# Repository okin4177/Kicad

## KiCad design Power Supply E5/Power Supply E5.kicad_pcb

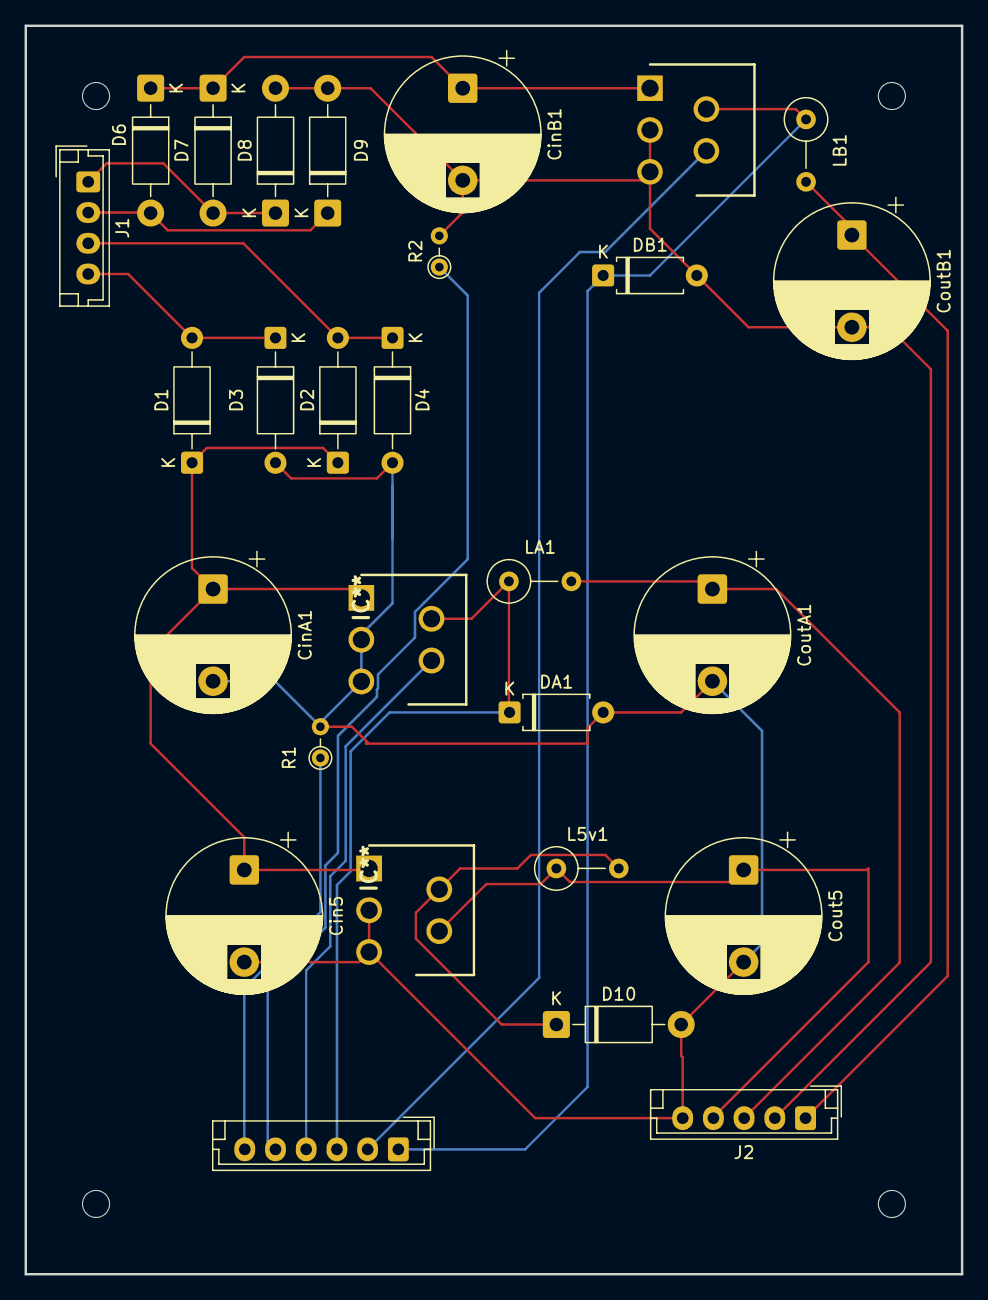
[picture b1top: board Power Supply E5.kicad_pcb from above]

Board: 2 copper layers, 76.2 x 101.6 mm, 30 parts (0 on the bottom side), 18 nets.

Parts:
Cin5: 100uF; CP_Radial_D12.5mm_P7.50mm
CinA1: 680uF; CP_Radial_D12.5mm_P7.50mm
CinB1: 100uF; CP_Radial_D12.5mm_P7.50mm
Cout5: 330uF; CP_Radial_D12.5mm_P7.50mm
CoutA1: 330uF; CP_Radial_D12.5mm_P7.50mm
CoutB1: 330uF; CP_Radial_D12.5mm_P7.50mm
D1, D2, D3, D4: 1N5059; D_A-405_P10.16mm_Horizontal
D6, D7, D8, D9: 1N4007; D_DO-41_SOD81_P10.16mm_Horizontal
D10: 1N5819; D_DO-41_SOD81_P10.16mm_Horizontal
DA1: 11DQ06; D_A-405_P7.62mm_Horizontal
DB1: 11DQ06; D_A-405_P7.62mm_Horizontal
IC**: TO170P470X1028X2142-5P; TO170P470X1028X2142-5P - Copy
IC**#2: TO170P470X1028X2142-5P; TO170P470X1028X2142-5P - Copy
J1: Conn_01x04; JST_EH_B4B-EH-A_1x04_P2.50mm_Vertical
J2: Conn_01x05; JST_EH_B5B-EH-A_1x05_P2.50mm_Vertical
J3: Conn_01x06; JST_EH_B6B-EH-A_1x06_P2.50mm_Vertical
L5v1: 330uH; L_Axial_L7.0mm_D3.3mm_P5.08mm_Vertical_Fastron_MICC
LA1: 330uH; L_Axial_L7.0mm_D3.3mm_P5.08mm_Vertical_Fastron_MICC
LB1: 330uH; L_Axial_L7.0mm_D3.3mm_P5.08mm_Vertical_Fastron_MICC
Q1, Q2: TL2575-05IKV; TO170P470X1016X2338-5P
Q**: TO170P470X1016X2338-5P
R1, R2: 700; R_Axial_DIN0204_L3.6mm_D1.6mm_P2.54mm_Vertical

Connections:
/5V: Cout5.1, IC**.4, J2.4, L5v1.1
/5/A COM: Cin5.2, CinA1.2, Cout5.2, CoutA1.2, D3.2 (A), D4.2 (A), D10.2 (A), DA1.2 (A), IC**.3, IC**.5, IC**#2.3, IC**#2.5, J2.5, R1.2
/-Ch B: CinB1.2, CoutB1.2, D8.2 (A), D9.2 (A), DB1.2 (A), J2.2, Q**.3, Q**.5, R2.2
/Ch A: CoutA1.1, J2.3, LA1.2
/Ch B: CoutB1.1, J2.1, LB1.2
/a+: D1.2 (A), D3.1 (K), J1.4
/a-: D2.2 (A), D4.1 (K), J1.3
/b+: D6.2 (A), D9.1 (K), J1.2
/b-: D7.2 (A), D8.1 (K), J1.1
/pot1: DA1.1 (K), IC**#2.2, J3.3, LA1.1
/pot1_l: J3.6, R1.1
/pot1w: IC**#2.4, J3.4
/pot2: DB1.1 (K), J3.1, LB1.1, Q**.2
/pot2_l: J3.5, R2.1
/pot2w: J3.2, Q**.4
unnamed: Cin5.1, CinA1.1, D1.1 (K), D2.1 (K), IC**.1, IC**#2.1
unnamed: CinB1.1, D6.1 (K), D7.1 (K), Q**.1
unnamed: D10.1 (K), IC**.2, L5v1.2

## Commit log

2025-10-16 Initial KiCad project commit
2025-10-16 Final changes were made before printing as pdf
